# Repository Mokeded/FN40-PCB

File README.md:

# FN40 PCB

KiCad PCB design for the **FN40**, a hotswap 40%-style mechanical keyboard (internal project name `4060`).

## Contents

- `4060.kicad_pro` / `4060.kicad_sch` / `4060.kicad_pcb` — KiCad project, schematic, and board files
- `4060.kicad_prl` — KiCad project local settings
- `4060.json` — layout/keyboard-layout-editor data
- `4060.svg` — rendered board image
- `4060.round-tracks-config` — config for the KiCad round-tracks plugin
- `4060-backups/` — autosaved backups of the board file
- `footprints/Switch_Keyboard_Hotswap_Kailh.pretty/` — Kailh hotswap socket footprint library
- `acheron_Components.pretty-master/`, `acheron_Connectors.pretty-master/` — third-party footprint libraries from [Acheron](https://github.com/acheron-project) (also kept as `.zip` archives)
- `random-keyboard-parts.pretty/` — additional footprint library
- `fp-lib-table` / `fp-info-cache` — KiCad footprint library table and cache
- `fabrication-toolkit-options.json` — settings for the [KiCad Fabrication Toolkit](https://github.com/bennymeg/kicad-fabrication-toolkit) plugin used to generate manufacturing files
- `freerouting.dsn` / `temp-freerouting.dsn` — Specctra DSN exports for autorouting with [Freerouting](https://github.com/freerouting/freerouting)
- `kbplacer.log` — log output from the [KiCad KBPlacer](https://github.com/adamws/kicad-kbplacer) plugin used for switch placement
- `production/` — generated manufacturing outputs, including `4060.zip` (Gerbers/drill files), `bom.csv` (bill of materials), `positions.csv` (pick-and-place data), `designators.csv`, and `netlist.ipc`

## Getting started

1. Install [KiCad](https://www.kicad.org/) (developed with KiCad 7/8).
2. Open `4060.kicad_pro` in KiCad.
3. Footprint libraries referenced by `fp-lib-table` are included in this repo — no extra setup should be required.

## Fabrication

Manufacturing-ready files (Gerbers, drill files, BOM, and pick-and-place data) are available in `production/`. These were generated with the KiCad Fabrication Toolkit plugin; re-run it after any board changes to refresh the outputs.

## Credits

- Footprint libraries by [Acheron](https://github.com/acheron-project)
- Hotswap socket footprints from the [Switch_Keyboard_Hotswap_Kailh](https://github.com/) footprint library

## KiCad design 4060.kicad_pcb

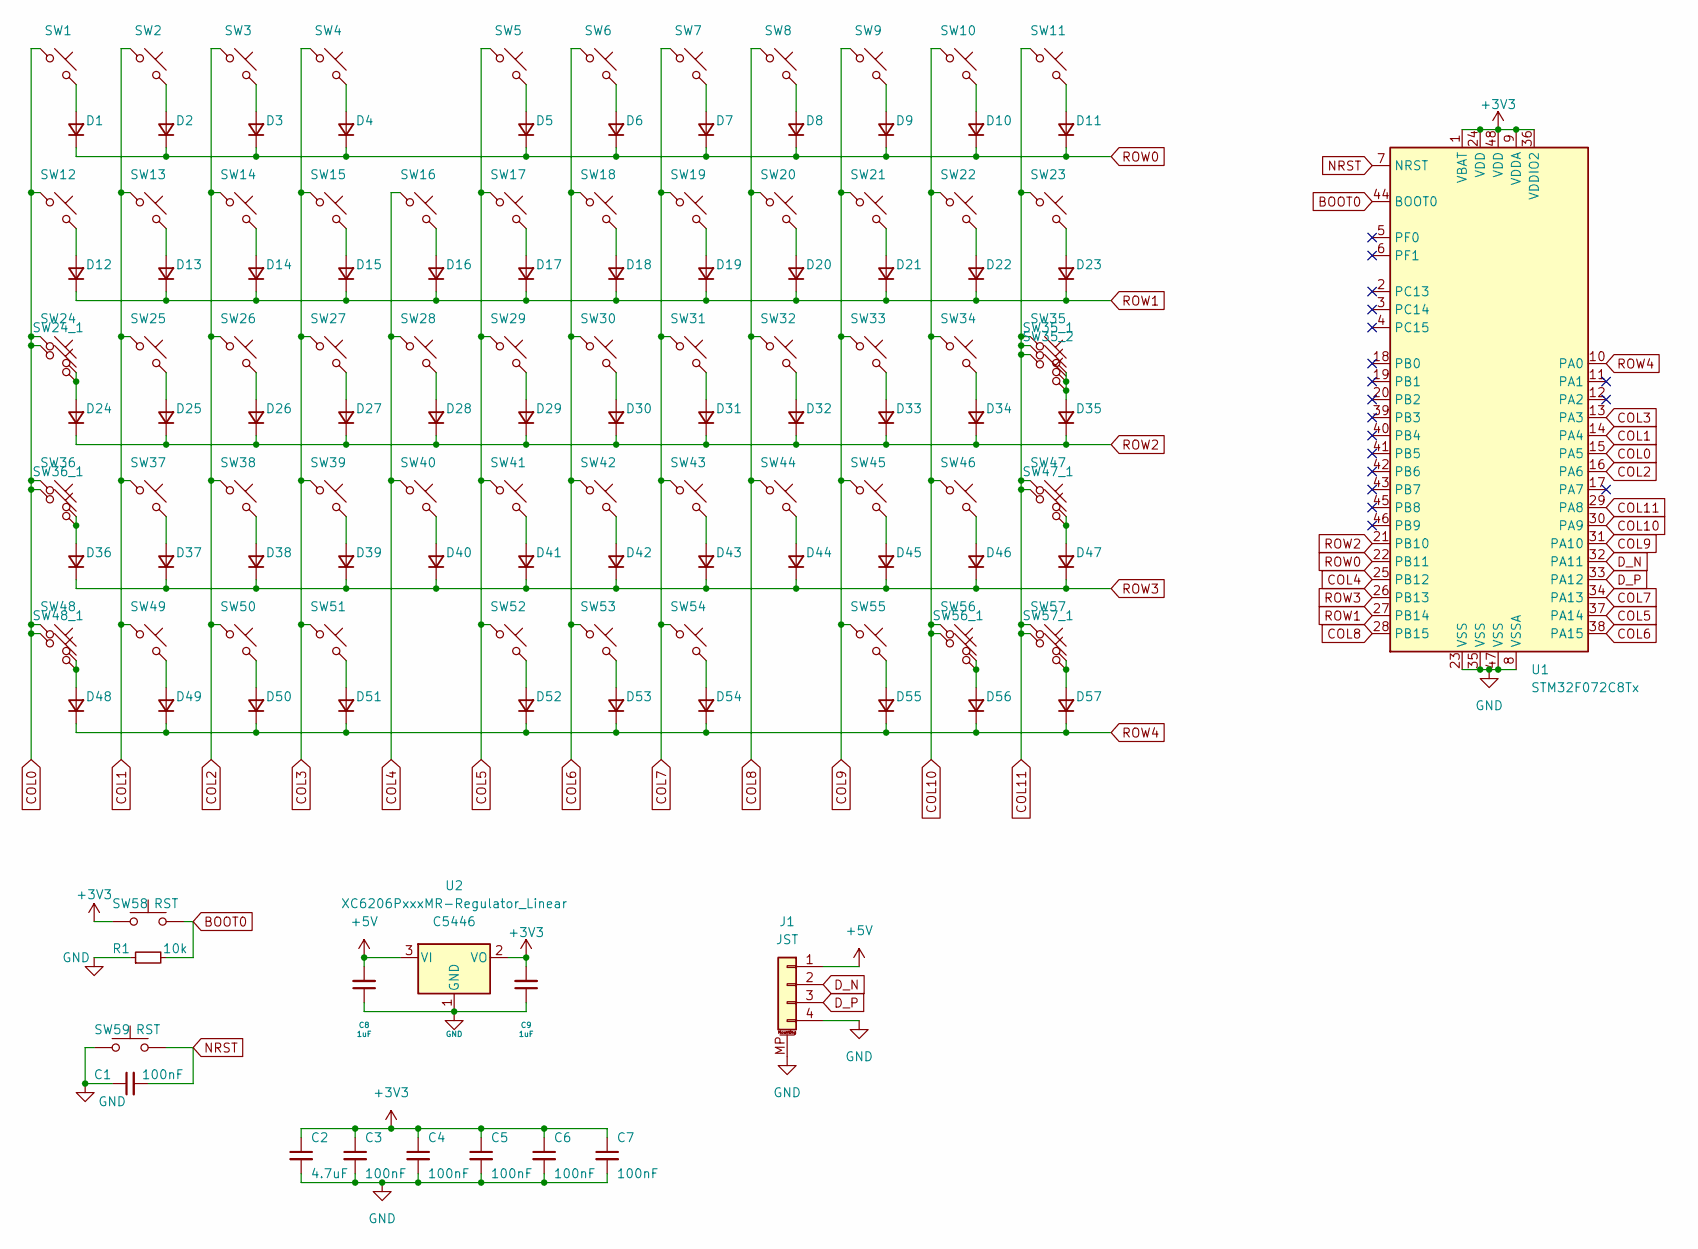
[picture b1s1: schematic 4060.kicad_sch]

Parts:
C1, C3, C4, C5, C6, C7: 100nF; C_0402_1005Metric; LCSC C307331
C2: 4.7uF; C_0402_1005Metric; LCSC C23733
C8, C9: 1uF; C_0402_1005Metric; LCSC C52923
D1, D2, D3, D4, D5, D6, D7, D8, D9, D10, D11, D12, D13, D14, D15, D16, D17, D18, D19, D20, D21, D22, D23, D24, D25, D26, D27, D28, D29, D30, D31, D32, D33, D34, D35, D36, D37, D38, D39, D40, D41, D42, D43, D44, D45, D46, D47, D48, D49, D50, D51, D52, D53, D54, D55, D56, D57: D; D_SOD-123F
J1: JST; MOLEX_781710004_MountingReliefs; LCSC C588524
R1: 10k; R_0402_1005Metric; LCSC C25744
SW1, SW2, SW3, SW4, SW5, SW6, SW7, SW8, SW9, SW10, SW11, SW13, SW14, SW15, SW16, SW17, SW18, SW19, SW20, SW21, SW22, SW25, SW26, SW27, SW28, SW29, SW30, SW31, SW32, SW33, SW34, SW37, SW38, SW39, SW40, SW41, SW42, SW43, SW44, SW45, SW46, SW50, SW51, SW55, SW56_1: SW_Push; SW_Hotswap_Kailh_MX_Plated_1.00u
SW12, SW23, SW48, SW49, SW56, SW57: SW_Push; SW_Hotswap_Kailh_MX_Plated_1.50u
SW24: SW_Push; SW_Hotswap_Kailh_MX_Plated_1.75u_90deg
SW24_1: SW_Push; SW_Hotswap_Kailh_MX_Plated_1.25u_90deg
SW35, SW36, SW48_1, SW57_1: SW_Push; SW_Hotswap_Kailh_MX_Plated_1.25u
SW35_1: SW_Push; SW_Hotswap_Kailh_MX_Plated_ISOEnter_270deg
SW35_2, SW36_1, SW54: SW_Push; SW_Hotswap_Kailh_MX_Plated_2.25u
SW47: SW_Push; SW_Hotswap_Kailh_MX_Plated_1.75u
SW47_1, SW52: SW_Push; SW_Hotswap_Kailh_MX_Plated_2.75u
SW53: SW_Push; SW_Hotswap_Kailh_MX_Plated_7.00u
SW58, SW59: RST; SW_SPST_SKQG_WithoutStem; LCSC C318884
U1: STM32F072C8Tx; LQFP-48_7x7mm_P0.5mm; LCSC C80488
U2: XC6206PxxxMR-Regulator_Linear; SOT-23; LCSC C5446

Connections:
+3V3: C2.1, C3.1, C4.1, C5.1, C6.1, C7.1, C9.2, SW58.1, U1.1 (VBAT), U1.9 (VDDA), U1.24 (VDD), U1.36 (VDDIO2), U1.48 (VDD), U2.2 (VO)
+5V: C8.2, J1.1, U2.3 (VI)
BOOT0: R1.2, SW58.2, U1.44 (BOOT0)
COL0: SW1.1, SW12.1, SW24.1, SW24_1.1, SW36.1, SW36_1.1, SW48.1, SW48_1.1, U1.15 (PA5)
COL1: SW2.1, SW13.1, SW25.1, SW37.1, SW49.1, U1.14 (PA4)
COL2: SW3.1, SW14.1, SW26.1, SW38.1, SW50.1, U1.16 (PA6)
COL3: SW4.1, SW15.1, SW27.1, SW39.1, SW51.1, U1.13 (PA3)
COL4: SW16.1, SW28.1, SW40.1, U1.25 (PB12)
COL5: SW5.1, SW17.1, SW29.1, SW41.1, SW52.1, U1.37 (PA14)
COL6: SW6.1, SW18.1, SW30.1, SW42.1, SW53.1, U1.38 (PA15)
COL7: SW7.1, SW19.1, SW31.1, SW43.1, SW54.1, U1.34 (PA13)
COL8: SW8.1, SW20.1, SW32.1, SW44.1, U1.28 (PB15)
COL9: SW9.1, SW21.1, SW33.1, SW45.1, SW55.1, U1.31 (PA10)
COL10: SW10.1, SW22.1, SW34.1, SW46.1, SW56.1, SW56_1.1, U1.30 (PA9)
COL11: SW11.1, SW23.1, SW35.1, SW35_1.1, SW35_2.1, SW47.1, SW47_1.1, SW57.1, SW57_1.1, U1.29 (PA8)
D_N: J1.2, U1.32 (PA11)
D_P: J1.3, U1.33 (PA12)
GND: C1.1, C2.2, C3.2, C4.2, C5.2, C6.2, C7.2, C8.1, C9.1, J1.4, J1.MP (MountPin), R1.1, SW59.1, U1.8 (VSSA), U1.23 (VSS), U1.35 (VSS), U1.47 (VSS), U2.1 (GND)
NRST: C1.2, SW59.2, U1.7 (NRST)
unnamed: D1.2 (A), SW1.2
unnamed: D2.2 (A), SW2.2
unnamed: D3.2 (A), SW3.2
unnamed: D4.2 (A), SW4.2
unnamed: D5.2 (A), SW5.2
unnamed: D6.2 (A), SW6.2
unnamed: D7.2 (A), SW7.2
unnamed: D8.2 (A), SW8.2
unnamed: D9.2 (A), SW9.2
unnamed: D10.2 (A), SW10.2
unnamed: D11.2 (A), SW11.2
unnamed: D12.2 (A), SW12.2
unnamed: D13.2 (A), SW13.2
unnamed: D14.2 (A), SW14.2
unnamed: D15.2 (A), SW15.2
unnamed: D16.2 (A), SW16.2
unnamed: D17.2 (A), SW17.2
unnamed: D18.2 (A), SW18.2
unnamed: D19.2 (A), SW19.2
unnamed: D20.2 (A), SW20.2
unnamed: D21.2 (A), SW21.2
unnamed: D22.2 (A), SW22.2
unnamed: D23.2 (A), SW23.2
unnamed: D24.2 (A), SW24.2, SW24_1.2
unnamed: D25.2 (A), SW25.2
unnamed: D26.2 (A), SW26.2
unnamed: D27.2 (A), SW27.2
unnamed: D28.2 (A), SW28.2
unnamed: D29.2 (A), SW29.2
unnamed: D30.2 (A), SW30.2
unnamed: D31.2 (A), SW31.2
unnamed: D32.2 (A), SW32.2
unnamed: D33.2 (A), SW33.2
unnamed: D34.2 (A), SW34.2
unnamed: D35.2 (A), SW35.2, SW35_1.2, SW35_2.2
unnamed: D36.2 (A), SW36.2, SW36_1.2
unnamed: D37.2 (A), SW37.2
unnamed: D38.2 (A), SW38.2
unnamed: D39.2 (A), SW39.2
unnamed: D40.2 (A), SW40.2
unnamed: D41.2 (A), SW41.2
unnamed: D42.2 (A), SW42.2
unnamed: D43.2 (A), SW43.2
unnamed: D44.2 (A), SW44.2
unnamed: D45.2 (A), SW45.2
unnamed: D46.2 (A), SW46.2
unnamed: D47.2 (A), SW47.2, SW47_1.2
unnamed: D48.2 (A), SW48.2, SW48_1.2
unnamed: D49.2 (A), SW49.2
unnamed: D50.2 (A), SW50.2
unnamed: D51.2 (A), SW51.2
unnamed: D52.2 (A), SW52.2
unnamed: D53.2 (A), SW53.2
unnamed: D54.2 (A), SW54.2
unnamed: D55.2 (A), SW55.2
unnamed: D56.2 (A), SW56.2, SW56_1.2
unnamed: D57.2 (A), SW57.2, SW57_1.2
ROW0: D1.1 (K), D2.1 (K), D3.1 (K), D4.1 (K), D5.1 (K), D6.1 (K), D7.1 (K), D8.1 (K), D9.1 (K), D10.1 (K), D11.1 (K), U1.22 (PB11)
ROW1: D12.1 (K), D13.1 (K), D14.1 (K), D15.1 (K), D16.1 (K), D17.1 (K), D18.1 (K), D19.1 (K), D20.1 (K), D21.1 (K), D22.1 (K), D23.1 (K), U1.27 (PB14)
ROW2: D24.1 (K), D25.1 (K), D26.1 (K), D27.1 (K), D28.1 (K), D29.1 (K), D30.1 (K), D31.1 (K), D32.1 (K), D33.1 (K), D34.1 (K), D35.1 (K), U1.21 (PB10)
ROW3: D36.1 (K), D37.1 (K), D38.1 (K), D39.1 (K), D40.1 (K), D41.1 (K), D42.1 (K), D43.1 (K), D44.1 (K), D45.1 (K), D46.1 (K), D47.1 (K), U1.26 (PB13)
ROW4: D48.1 (K), D49.1 (K), D50.1 (K), D51.1 (K), D52.1 (K), D53.1 (K), D54.1 (K), D55.1 (K), D56.1 (K), D57.1 (K), U1.10 (PA0)

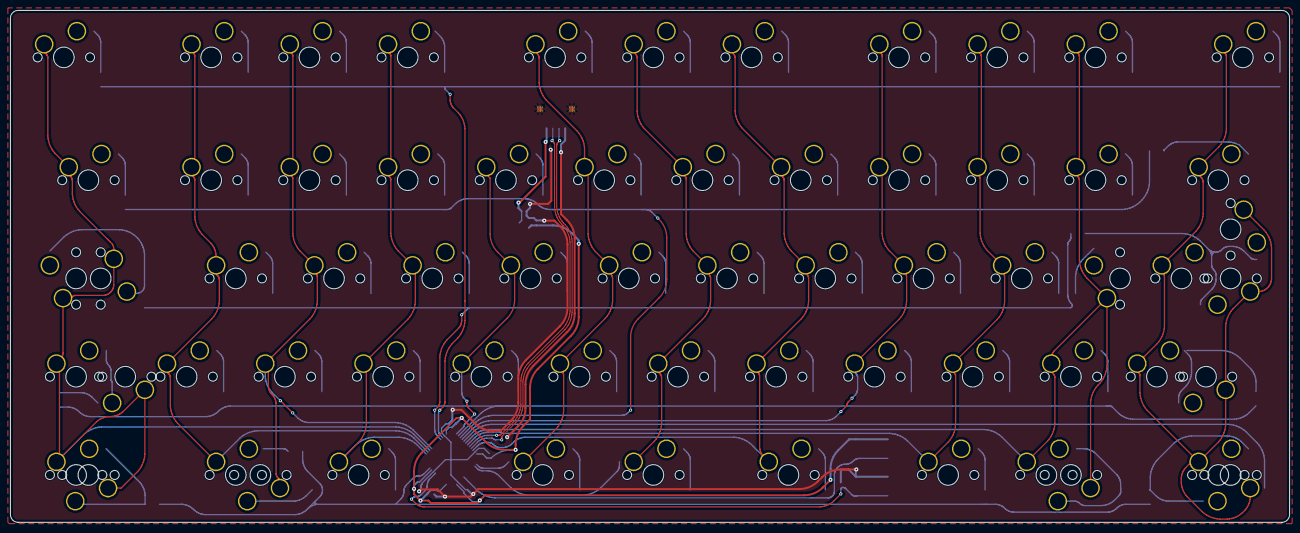
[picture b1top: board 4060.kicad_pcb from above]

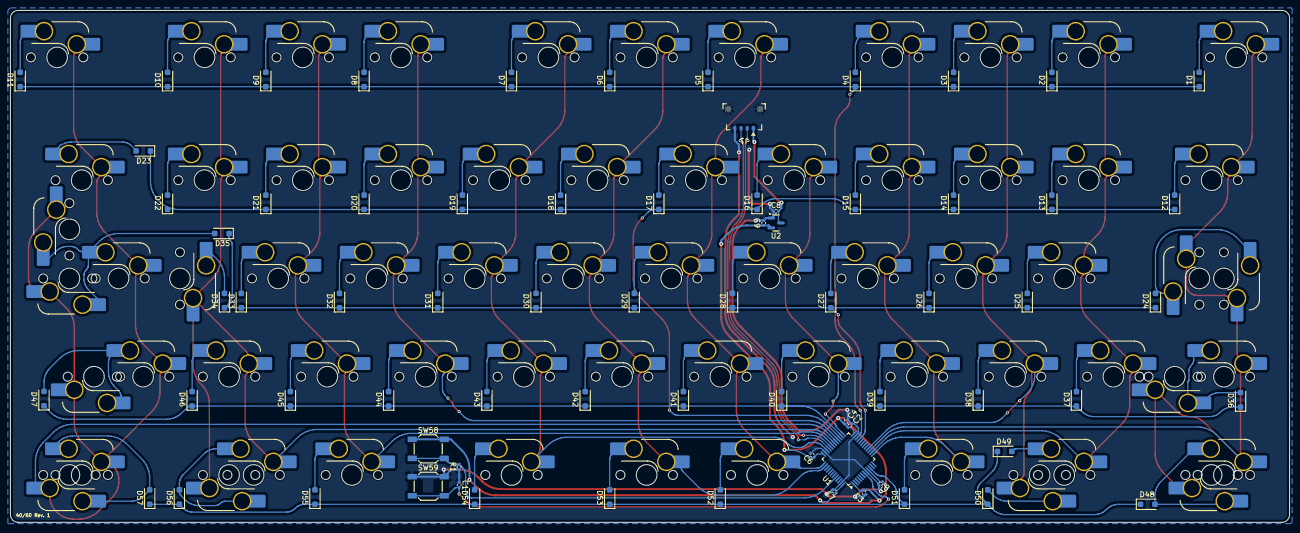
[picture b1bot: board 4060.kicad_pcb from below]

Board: 2 copper layers, 248.0 x 99.2 mm, 137 parts (72 on the bottom side), 81 nets.

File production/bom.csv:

Designator,Footprint,Quantity,Value,LCSC Part #
"C1, C3, C4, C5, C6, C7",0402,6,100nF,C307331
C2,0402,1,4.7uF,C23733
"C8, C9",0402,2,1uF,C52923
"D1, D10, D11, D12, D13, D14, D15, D16, D17, D18, D19, D2, D20, D21, D22, D23, D24, D25, D26, D27, D28, D29, D3, D30, D31, D32, D33, D34, D35, D36, D37, D38, D39, D4, D40, D41, D42, D43, D44, D45, D46, D47, D48, D49, D5, D50, D51, D52, D53, D54, D55, D56, D57, D6, D7, D8, D9",D_SOD-123F,57,D,
J1,MOLEX_781710004_MountingReliefs,1,JST,C588524
R1,0402,1,10k,C25744
"SW1, SW10, SW11, SW13, SW14, SW15, SW16, SW17, SW18, SW19, SW2, SW20, SW21, SW22, SW25, SW26, SW27, SW28, SW29, SW3, SW30, SW31, SW32, SW33, SW34, SW37, SW38, SW39, SW4, SW40, SW41, SW42, SW43, SW44, SW45, SW46, SW5, SW50, SW51, SW55, SW56_1, SW6, SW7, SW8, SW9",SW_Hotswap_Kailh_MX_Plated_1.00u,45,SW_Push,
"SW12, SW23, SW48, SW49, SW56, SW57",SW_Hotswap_Kailh_MX_Plated_1.50u,6,SW_Push,
SW24,SW_Hotswap_Kailh_MX_Plated_1.75u_90deg,1,SW_Push,
SW24_1,SW_Hotswap_Kailh_MX_Plated_1.25u_90deg,1,SW_Push,
"SW35, SW36, SW48_1, SW57_1",SW_Hotswap_Kailh_MX_Plated_1.25u,4,SW_Push,
SW35_1,SW_Hotswap_Kailh_MX_Plated_ISOEnter_270deg,1,SW_Push,
"SW35_2, SW36_1, SW54",SW_Hotswap_Kailh_MX_Plated_2.25u,3,SW_Push,
SW47,SW_Hotswap_Kailh_MX_Plated_1.75u,1,SW_Push,
"SW47_1, SW52",SW_Hotswap_Kailh_MX_Plated_2.75u,2,SW_Push,
SW53,SW_Hotswap_Kailh_MX_Plated_7.00u,1,SW_Push,
"SW58, SW59",SW_SPST_SKQG_WithoutStem,2,RST,C318884
U1,LQFP-48_7x7mm_P0.5mm,1,STM32F072C8Tx,C80488
U2,SOT-23,1,XC6206PxxxMR-Regulator_Linear,C5446

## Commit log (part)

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2026-02-18 Added files
2026-02-19 Added MCU, ESD, and some routing
2026-02-20 Finished PCB
2026-02-21 Routing fixes
